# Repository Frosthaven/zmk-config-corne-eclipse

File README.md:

README | [Keymap](KEYMAP.md) | [MX Parts](PARTS_MX.md) | [Building](BUILDING.md) | [Tricks](TRICKS.md)

# Corne Eclipse

---

The Corne Eclipse is a highly customized wireless Corne MX.

*This was a project I initially finished in 2021. Finally updated and open sourced!*

## Custom Circuit Board Design

- JST port with line passthrough for undercarriage battery storage
- Native support for dual nice!view displays
- Native support for dual Alps EC11/EC12 encoders
- Native support for Azoteq TPS43 trackpad (right half, replaces encoder and display)
- Native support for side mounted power switches
- Native support for tenting puck

## Custom Shield Casing Design

Based on Void's case.

- Undercarriage battery storage
- Optimized material usage for bottom
- Native support for tenting puck

## Peripheral-side Trackpad Support

- TPS43 (and related Azoteq IQS5xx modules) via [AYM1607/zmk-driver-azoteq-iqs5xx](https://github.com/AYM1607/zmk-driver-azoteq-iqs5xx)
- Cirque Touchpad via [petejohanson/cirque-input-module](https://github.com/petejohanson/cirque-input-module)

## ZMK Modifications

### External Display Upgrades

- Lithium curve LUT applied for a 403450 to get more accurate numeric charge data (PR reference: [ZMK PR 2066](https://github.com/zmkfirmware/zmk/pull/2066))
- Track battery status of both halves on a single nice!view
- Capslock indicator

### RGB Battery Optimizations

Powered by [zmk-ext-power-smart-idle](https://github.com/Frosthaven/zmk-ext-power-smart-idle).

- 20% brightness when not plugged in
- RGB auto-off on low battery when not plugged in
- Lights stay on when plugged in
- Eclipse v3 reversible variant uses a MOSFET that prevents drain when LEDs are off (coming soon)

## Default Typing Layouts

Available in [releases](https://github.com/Frosthaven/zmk-config-corne-eclipse/releases).

- QWERTY
- Colemak Mod DH (personal choice!)
- Colemak
- Workman
- DVORAK

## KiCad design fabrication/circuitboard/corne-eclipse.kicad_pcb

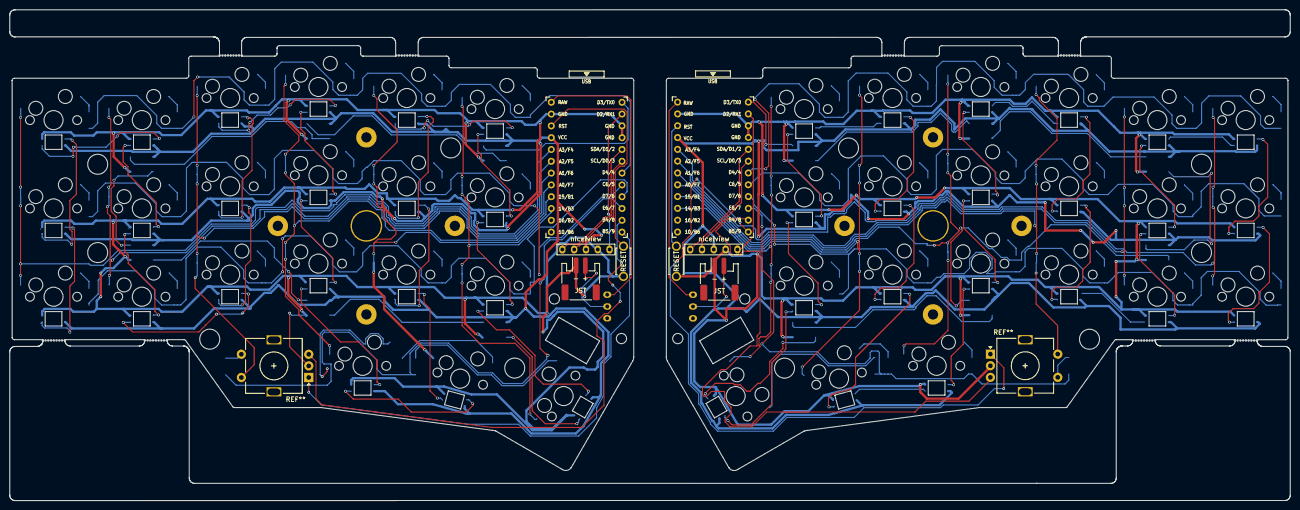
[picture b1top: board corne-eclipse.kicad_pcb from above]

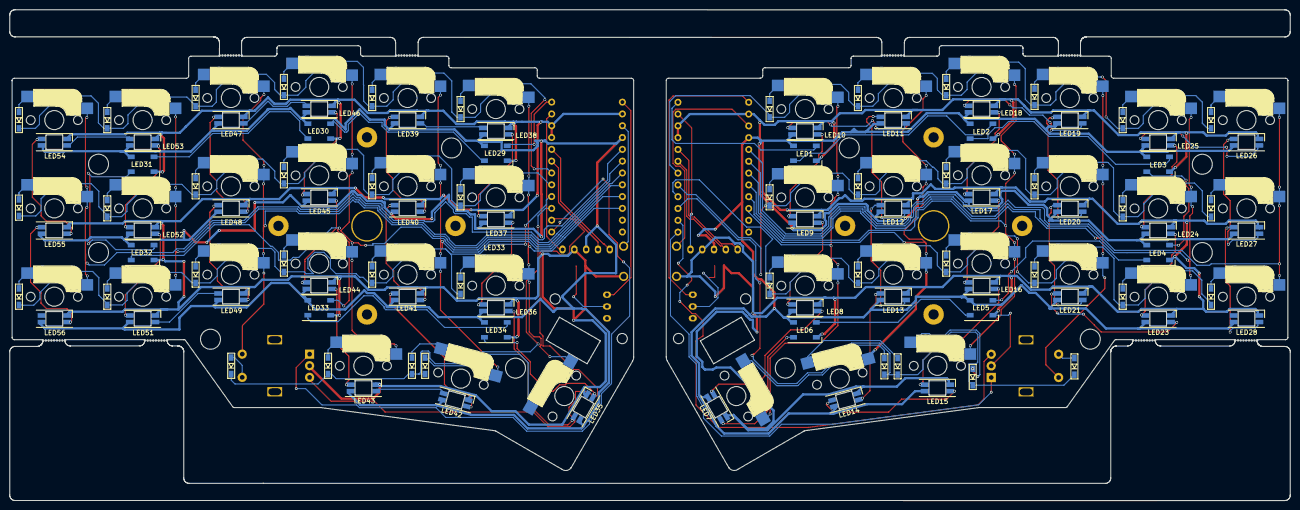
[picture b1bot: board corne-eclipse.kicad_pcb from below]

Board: 2 copper layers, 275.5 x 105.6 mm, 166 parts (101 on the bottom side), 125 nets.

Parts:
D1, D2, D3, D4, D5, D6, D7, D8, D9, D10, D11, D12, D13, D14, D15, D16, D17, D18, D19, D19#2, D20, D21, D22, D23, D24, D25, D26, D27, D28, D29, D30, D31, D32, D33, D34, D35, D36, D37, D38, D39, D40, D40#2, D41, D42: D; D3_SMD_v2
J2, J4: OLED; nice!view
JST: JST_PH_S2B-PH-SM4-TB_1x02-1MP_P2.00mm_Horizontal
JST#2: JST_PH_S2B-PH-SM4-TB_1x02-1MP_P2.00mm_Horizontal
LED1, LED2, LED3, LED4, LED5, LED6, LED29, LED30, LED31, LED32, LED33, LED33#2: WS2812B; LED_WS2812B_PLCC4_5.0x5.0mm_P3.2mm
LED7, LED8, LED9, LED10, LED11, LED12, LED13, LED14, LED15, LED16, LED17, LED18, LED19, LED20, LED21, LED23, LED24, LED25, LED26, LED27, LED28, LED35, LED36, LED37, LED38, LED39, LED40, LED41, LED42, LED43, LED44, LED45, LED46, LED47, LED48, LED49, LED51, LED52, LED53, LED54, LED55, LED56: YS-SK6812MINI-E
PWR: power
PWR#2: power
RSW1, RSW1#2: SW_PUSH; ResetSW_1side
Ref**: Val**; M2_HOLE_v2
Ref**#2, Ref**#3, Ref**#4, Ref**#5, Ref**#6, Ref**#7, Ref**#8, Ref**#9, Ref**#10, Ref**#11, Ref**#12, Ref**#13, Ref**#14: Val**; M2_HOLE_v2
SW1, SW2, SW3, SW4, SW5, SW6, SW7, SW8, SW9, SW10, SW11, SW12, SW13, SW14, SW15, SW16, SW17, SW18, SW19, SW20, SW21, SW23, SW24, SW25, SW26, SW27, SW28, SW29, SW30, SW31, SW32, SW33, SW34, SW35, SW36, SW37, SW38, SW39, SW40, SW41, SW42, SW43: SW_PUSH; CherryMX_Hotswap
SW22, SW44: SW_PUSH; CherryMX_Hotswap_1.5u
U1, U2: nice!nano; ProMicro_v3

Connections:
GND: J2.4, LED1.3, LED2.3, LED3.3, LED4.3, LED5.3, LED6.3, LED7.3, LED8.3, LED9.3, LED10.3, LED11.3, LED12.3, LED13.3, LED14.3, LED15.3, LED16.3, LED17.3, LED18.3, LED19.3, LED20.3, LED21.3, LED23.3, LED24.3, LED25.3, LED26.3, LED27.3, LED28.3, U1.3, U1.4, U1.23
GNDA: J4.4, LED29.3, LED30.3, LED31.3, LED32.3, LED33.3, LED33#2.3, LED35.3, LED36.3, LED37.3, LED38.3, LED39.3, LED40.3, LED41.3, LED42.3, LED43.3, LED44.3, LED45.3, LED46.3, LED47.3, LED48.3, LED49.3, LED51.3, LED52.3, LED53.3, LED54.3, LED55.3, LED56.3, U2.3, U2.4, U2.23
LED_r: LED29.prev, U2.1
unnamed: D1.2, SW1.2
unnamed: D2.2, SW2.2
unnamed: D3.2, SW3.2
unnamed: D4.2, SW4.2
unnamed: D5.2, SW5.2
unnamed: D6.2, SW6.2
unnamed: D7.2, SW7.2
unnamed: D8.2, SW8.2
unnamed: D9.2, SW9.2
unnamed: D10.2, SW10.2
unnamed: D11.2, SW11.2
unnamed: D12.2, SW12.2
unnamed: D13.2, SW13.2
unnamed: D14.2, SW14.2
unnamed: D15.2, SW15.2
unnamed: D16.2, SW16.2
unnamed: D17.2, SW17.2
unnamed: D18.2, SW18.2
unnamed: D19.2, SW20.2
unnamed: D20.2, SW21.2
unnamed: D21.2, SW22.2
unnamed: D22.2, SW23.2
unnamed: D23.2, SW24.2
unnamed: D24.2, SW25.2
unnamed: D25.2, SW26.2
unnamed: D26.2, SW27.2
unnamed: D27.2, SW28.2
unnamed: D28.2, SW29.2
unnamed: D29.2, SW30.2
unnamed: D30.2, SW31.2
unnamed: D31.2, SW32.2
unnamed: D32.2, SW33.2
unnamed: D33.2, SW34.2
unnamed: D34.2, SW35.2
unnamed: D35.2, SW36.2
unnamed: D36.2, SW37.2
unnamed: D37.2, SW38.2
unnamed: D38.2, SW39.2
unnamed: D39.2, SW40.2
unnamed: D40.2, SW42.2
unnamed: D41.2, SW43.2
unnamed: D42.2, SW44.2
SCL: J2.2, U1.6
SCL_r: J4.2, U2.6
SDA: J2.1, U1.5
SDA_r: J4.1, U2.5
VCC: J2.3, LED1.1, LED2.1, LED3.1, LED4.1, LED5.1, LED6.1, LED7.1, LED8.1, LED9.1, LED10.1, LED11.1, LED12.1, LED13.1, LED14.1, LED15.1, LED16.1, LED17.1, LED18.1, LED19.1, LED20.1, LED21.1, LED23.1, LED24.1, LED25.1, LED26.1, LED27.1, LED28.1, U1.21
VDD: J4.3, LED29.1, LED30.1, LED31.1, LED32.1, LED33.1, LED33#2.1, LED35.1, LED36.1, LED37.1, LED38.1, LED39.1, LED40.1, LED41.1, LED42.1, LED43.1, LED44.1, LED45.1, LED46.1, LED47.1, LED48.1, LED49.1, LED51.1, LED52.1, LED53.1, LED54.1, LED55.1, LED56.1, U2.21
col0: SW1.1, SW7.1, SW13.1, U1.20
col0_r: SW23.1, SW29.1, SW35.1, U2.20
col1: SW2.1, SW8.1, SW14.1, U1.19
col1_r: SW24.1, SW30.1, SW36.1, U2.19
col2: SW3.1, SW9.1, SW15.1, U1.18
col2_r: SW25.1, SW31.1, SW37.1, U2.18
col3: SW4.1, SW10.1, SW16.1, SW20.1, U1.17
col3_r: SW26.1, SW38.1, SW42.1, U2.17
col4: SW5.1, SW11.1, SW17.1, SW21.1, U1.16
col4_r: SW27.1, SW33.1, SW39.1, SW43.1, U2.16
col5: SW6.1, SW12.1, SW18.1, SW22.1, U1.15
col5_r: SW28.1, SW34.1, SW40.1, SW44.1, U2.15
data: J2.5, U1.2
data_r: J4.5, U2.2
led1-led2: LED1.next, LED2.prev
led2-led3: LED2.next, LED3.prev
led3-led4: LED3.next, LED4.prev
led4-led5: LED4.next, LED5.prev
led5-led6: LED5.next, LED6.prev
led6-led7: LED6.next, LED7.prev
led7-led8: LED7.next, LED8.prev
led8-led9: LED8.next, LED9.prev
led9-led10: LED9.next, LED10.prev
led10-led11: LED10.next, LED11.prev
led11-led12: LED11.next, LED12.prev
led12-led13: LED12.next, LED13.prev
led13-led14: LED13.next, LED14.prev
led14-led15: LED14.next, LED15.prev
led15-led16: LED15.next, LED16.prev
led16-led17: LED16.next, LED17.prev
led17-led18: LED17.next, LED18.prev
led18-led19: LED18.next, LED19.prev
led19-led20: LED19.next, LED20.prev
led20-led21: LED20.next, LED21.prev
led21-led23: LED21.next, LED23.prev
led23-led24: LED23.next, LED24.prev
led24-led25: LED24.next, LED25.prev
led25-led26: LED25.next, LED26.prev
led26-led27: LED26.next, LED27.prev
led27-led28: LED27.next, LED28.prev
led29-led30: LED29.next, LED30.prev
led30-led31: LED30.next, LED31.prev
led31-led32: LED31.next, LED32.prev
led32-led33: LED32.next, LED33.prev
led33-led34: LED33.next, LED33#2.prev
led34-led35: LED33#2.next, LED35.prev
led35-led36: LED35.next, LED36.prev
led36-led37: LED36.next, LED37.prev
led37-led38: LED37.next, LED38.prev
led38-led39: LED38.next, LED39.prev
led39-led40: LED39.next, LED40.prev
led40-led41: LED40.next, LED41.prev
led41-led42: LED41.next, LED42.prev
led42-led43: LED42.next, LED43.prev
led43-led44: LED43.next, LED44.prev
led44-led45: LED44.next, LED45.prev
led45-led46: LED45.next, LED46.prev
led46-led47: LED46.next, LED47.prev
led47-led48: LED47.next, LED48.prev
led48-led49: LED48.next, LED49.prev
led49-led51: LED49.next, LED51.prev
led51-led52: LED51.next, LED52.prev
led52-led53: LED52.next, LED53.prev
led53-led54: LED53.next, LED54.prev
led54-led55: LED54.next, LED55.prev
led55-led56: LED55.next, LED56.prev
row0: D1.1, D2.1, D3.1, D4.1, D5.1, D6.1, U1.7
row0_r: D22.1, D23.1, D24.1, D25.1, D26.1, D27.1, U2.7
row1: D7.1, D8.1, D9.1, D10.1, D11.1, D12.1, U1.8
row1_r: D28.1, D29.1, D30.1, D31.1, D32.1, D33.1, U2.8
row2: D13.1, D14.1, D15.1, D16.1, D17.1, D18.1, U1.9
row2_r: D34.1, D35.1, D36.1, D37.1, D38.1, D39.1, U2.9
row3: D19.1, D19#2.1, D20.1, D21.1, U1.10
row3_r: D40.1, D40#2.1, D41.1, D42.1, U2.10

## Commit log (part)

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2026-03-28 Import project
2026-03-28 Multi-Layout Builds
2026-03-28 docs: added back image
2026-03-28 fix: invert samurai display image palette
2026-03-28 chore: update image
2026-03-28 chore: image cleanup
2026-03-28 chore: remove dispatch checkboxes, always include everything
2026-03-28 chore: rework NAVPAD layer navigation keys
    Remove cross-platform line start/end macros in favor of plain Home/End
    keys. Reorganize nav cluster: Home/End replace macros, PgUp/PgDn shift
    inward, add PrintScreen/Insert/PauseBreak, swap NumLock/ScrollLock.
2026-03-28 docs(keymap): added macos modifier key notes
2026-03-28 fix(docs): adjust keymap headings
2026-03-28 docs(keymap): added notes for linux
2026-03-29 fix:keymap.md
2026-03-29 feat(keymap): updated references
2026-03-29 docs: update
2026-03-29 fix(ci): show all commits since last published release and add keymap link
    Release notes were only showing the last commit because gh release list
    included draft releases. Added --exclude-drafts flag and a versioned
    keymap image link pinned to the build's commit SHA.
2026-03-29 chore:docs
2026-03-29 fix(ci): fetch full git history for release notes
    Shallow clone (default depth 1) meant git log could only see one commit.
    Set fetch-depth: 0 to get full history for generating release notes.
2026-03-29 fix(keymap): fixed transparent issues on gui and alt (moved app menu)
2026-04-22 feat(nice!view): show ".." for stale battery readings post-unplug
    Right after USB unplug, the cached battery percentage is still inflated
    from the charging voltage and stays that way until the next ADC poll
    catches the relaxed reading. Show ".." in place of the number during
    that window so we don't display a misleading value.
    Per-cell "stale" tracking in the widget: on charging->not transition,
    snapshot the displayed level as a baseline and set stale=true. Clear
2026-05-18 wip(reversible)
2026-05-18 feat(conf): enable render-layer runtime brightness cap
2026-05-19 docs(karabiner): drop "Left" qualifier from tap-Raycast rule
    The Corne Eclipse only has one Command key (LGUI), so "Left Command"
    was misleading. Rename the rule description and KEYMAP entries to
    just "Command".
2026-05-20 feat(widgets): show ".." on battery cells while settling at boot
2026-05-24 feat(trackpad): forward peripheral trackpad over input-split; scenario-folder builds
    A pointing device on a split peripheral must forward its input to the
    central via zmk,input-split -- a plain input-listener on the peripheral
    never reaches the HID host. Add the input-split proxies + listeners and
    switch the overlays to TRACKPAD_PERIPHERAL / TRACKPAD_CENTRAL scenario
    flags (peripheral forwards, central receives; or central hosts locally).
    Restructure the build matrix into 6 variants per layout and group the
2026-05-24 feat(trackpad): relocate central status to the peripheral display
    When the trackpad is on the central (left) half it has no display, so the
    central forwards its status (layer/profile/WPM/caps) over the new split
    characteristic and the peripheral renders it in a left-hand panel beside
    the battery row (replacing the logo). Enabled via
    CONFIG_ZMK_SPLIT_CENTRAL_STATUS_MIRROR on the trackpad_central pair only;
    standard and peripheral-trackpad builds are unaffected (logo as before).
2026-05-24 feat(trackpad): zoom (pinch+expand) + double-tap-drag
    Point west.yml at the Frosthaven azoteq driver fork (gestures branch) which
    adds the two-finger zoom gesture and double-tap-and-drag. Enable 'zoom' and
    'drag-requires-double-tap' on the trackpad node, and on the central map the
    driver's zoom codes (INPUT_REL_MISC=expand, INPUT_REL_DIAL=pinch) to Ctrl +
    scroll via tp_zoom_in/out macros + a zmk,input-processor-behaviors processor,
    attached to the input-split receiver (peripheral trackpad) and the local
2026-05-24 build(debug): temporary right-half firmware with USB + gesture logging
    Captures the Azoteq chip's gesture bytes + finger coords during a pinch to
    diagnose why zoom isn't firing. Remove once zoom is fixed.
2026-05-24 fix(trackpad): switch-xy instead of flip-x (corrects 90-degree cursor rotation)
2026-05-24 feat(trackpad): three-finger-tap middle click; drag-lock + zoom retune; drop zoom-test build
    Enable three-finger-tap on the trackpad node, remove the temporary zoom-test
    build variant (real zoom is now in the normal firmware via the driver fork).
2026-05-24 fix(trackpad): correct cursor orientation (switch-xy -> flip-x)
    Computed from the observed direction mapping with switch-xy active; flip-x alone
    maps each finger direction to the matching cursor direction (and is independent
    of the chip's transform order). Replaces the physical-rotation workaround.
2026-05-24 build: pin azoteq driver to exact SHA to defeat stale CI module cache
    The CI caches west modules keyed on hashFiles(west.yml, build.yaml) and runs
    'west update --fetch smart'. Driver-only commits to the 'gestures' branch
    changed neither file, so builds silently reused a stale cached driver checkout
    (branch HEAD moved, smart-fetch skipped it). Pinning the exact commit changes
    west.yml on every driver bump -> cache key changes -> fresh fetch of the right
    code. This is the first build to actually include the driver gesture rework.
2026-05-24 feat(trackpad): press-and-hold drag-lock (drag-lock prop); zoom 20
    Bump pinned driver SHA to 3a49e00; rename overlay drag-requires-double-tap ->
    drag-lock; update WIRING_TRACKPAD to press-and-hold drag-lock + experimental zoom.
2026-05-24 build: bump azoteq driver SHA to 33c87bd (pinch != right-click + zoom sensitivity)
2026-05-24 feat(trackpad): port updated input-split gesture firmware to main
    Bring the peripheral-trackpad input-split architecture + forked gesture driver
    to main (overlays, dtsi, west.yml driver pin, central-status widgets, scenario
    build variants for all 5 layouts, release workflow, wiring doc). main's old
    USE_TRACKPAD/direct-listener scheme couldn't support a peripheral-side trackpad.
    Fabrication files, keymap, and docs are untouched.
2026-05-24 revert(encoder): left_encoder steps back to 20
    steps was the wrong lever for volume granularity: the per-event volume step is
    OS-controlled (the keyboard only sends volume up/down). steps=80 just made the
    encoder fire a volume event every ~2-6 clicks (less responsive) without changing
    the step. Back to 20 = one volume event per click. Battery LUT fix stays.
2026-05-25 feat(encoder): right encoder zooms (Ctrl+scroll) on trackpad builds
    Gate the right encoder per build: trackpad firmware (TRACKPAD_PERIPHERAL or
    TRACKPAD_CENTRAL) zooms via Ctrl + mouse-scroll (zoom_in/zoom_out macros driven
    by a zoom_encoder sensor-rotate); plain 'no trackpads' builds keep their prior
    scroll_vertical/scroll_horizontal behavior. Left encoder stays volume.
2026-05-25 fix(encoder): steps 40 for EC12 (one trigger per detent)
    EC12 encoders have 4 quadrature edges per detent. With steps=20 and
    triggers-per-rotation=10 the driver emitted 2 triggers per detent (one
    mid-click, one at the click). steps=40 makes 4*10/40 = exactly one trigger
    per physical detent. Frosthaven hardware only; Ashley's encoders may differ.
2026-05-25 docs(encoder): note EC12 tuning is active + EC11 values
    Comment-only; document that steps/triggers-per-rotation are tuned for the EC12
    on this board, with the EC11 (2 edges/detent) alternative inline. No firmware
    change.
2026-05-25 fix(encoder): steps=72 (whole-number deg/edge + more margin)
    steps=76 still dropped some detents. 360/76 is fractional (4.73 deg/edge), so the
    sensor math carries a remainder that truncates differently CW vs CCW and can drop
    clicks. steps=72 gives 360/72 = 5 deg/edge exactly (no fractional remainder) and
    20 deg/detent (2 deg over the 18 deg threshold). Trade is a rare double every ~9
    detents on continuous spinning. Frosthaven hardware only.
2026-05-25 fix(encoder): steps=64 (balance point between miss/double)
    steps=60 over-fired (1.11/detent: 3 doubles, 1 miss in 18); steps=72 under-fired
    (0.76). The encoder emits inconsistent edges/detent so 1:1 isn't perfectly
    achievable; steps=64 targets the avg~1.0 minimum-error point. Frosthaven only.
2026-05-25 docs(encoder): record steps=64 verified clean 1:1 on hardware
    Comment-only; steps=64 confirmed 20/20 detents both directions. No firmware
    change (build-163 already has steps=64).
2026-05-25 Revert "test(encoder): drop GPIO_PULL_UP + steps=80 (zmk#2666 signal fix)"
    This reverts commit 3b4a487a33f5f46a47dfe962cd64ef0061fd306f.
2026-05-25 revert(encoder): drop trackpad-zoom; restore per-layer scroll + EC12 96/24
    The right-encoder Ctrl+scroll zoom (gated on trackpad builds) is removed: the
    encoder's edge jitter made zoom unreliable. Right encoder returns to plain
    scroll_vertical / scroll_horizontal per layer as before (removed the gate,
    zoom_encoder behavior, and zoom_in/out macros).
    Also corrects the EC12 tuning to the datasheet-faithful 24/24 values:
    triggers-per-rotation=24 (detents), steps=96 (4x). Pull-up retained (board has
2026-05-25 ci(build): only draft a release on main builds
    Gate the release job with 'if: github.ref == refs/heads/main' so dispatching the
    build against other branches (e.g. v3-choc-mx) still compiles firmware but does
    not create a draft release. Applies on all forks/branches.
2026-05-26 build(west): bump zmk to d5963f2 (smart-idle before input-split chars)
    Fixes central->peripheral idle-activity sync on trackpad-on-peripheral builds.
    The central previously never discovered the smart-idle write handle (it sat
    after the input-split characteristics, which the central's input-descriptor
    discovery doesn't continue past), so it silently skipped the cross-half wake
    write. The fork now orders the smart-idle characteristic before the input-split
    chars and records the write handle without subscribing to NOTIFY.
2026-05-27 build(west): bump azoteq driver to 35fac92 (scroll no longer right-clicks)
    The IQS5xx driver now treats any moving two-finger touch as a scroll/zoom
    attempt rather than a tap, so a short two-finger scroll can no longer be
    misclassified as a two-finger tap (right click) on lift.
2026-06-15 build(west): bump cirque + azoteq forks for trackpad PM device support
    Pulls cirque-input-module fork at c9d41b4 (petejohanson's
    feat/idle-waker-wake-from-sleep-fixes cherry-picked) and zmk-driver-azoteq-iqs5xx
    gestures branch at 9c6f2be (new iqs5xx_pm_action). Both drivers now handle
    PM_DEVICE_ACTION_RESUME by re-applying chip config and re-arming their
    data-ready GPIO interrupt -- the trackpad recovers cleanly when the SoC wakes
    from CONFIG_ZMK_SLEEP, no more 'dead until power-cycle' after a long idle.
2026-06-18 feat(trackpad): slow Azoteq cursor 50% (cursor-scale-percent 75 -> 50)
2026-06-18 feat(encoder): right encoder always scrolls (drop trackpad zoom mode)
    The right encoder previously emitted Ctrl+scroll on trackpad builds
    (via the zoom_encoder behavior and zoom_in/zoom_out macros) and
    plain scroll otherwise. With the trackpad's two-finger scroll
    covering the same gesture, the encoder doesn't need to double as a
    zoom wheel -- unify on scroll for all builds.
    Collapse the TRACKPAD_PERIPHERAL/CENTRAL conditional in the keymap;
2026-06-18 fix(west): bump azoteq SHA to ddda9f8 (race fix; missed in earlier commit)
2026-06-18 build(west): bump azoteq to d412c57
    Cursor: per-axis fractional accumulator preserves slow precision
    motion (the integer scale used to round chip deltas of 1 to zero
    at scale<100, leaving a dead zone for granular selection).
    Scroll: cursor-scale-percent now applies to the wheel divisor too
    so the slowdown matches.
    Tap-then-hold: engage window 250ms -> 200ms (feels like a
2026-06-18 build(west): bump azoteq to 870a830
    Fixes double-tap eating: tap-then-hold engagement now waits for
    motion before latching LEFT, so a quick second tap lifts cleanly
    through the normal tap path as a second click. emit_click also
    release-firsts a still-held button so fast taps land as two
    distinct clicks.
    Halves the scroll slowdown vs cursor (cursor=50 -> scroll_div=42,
